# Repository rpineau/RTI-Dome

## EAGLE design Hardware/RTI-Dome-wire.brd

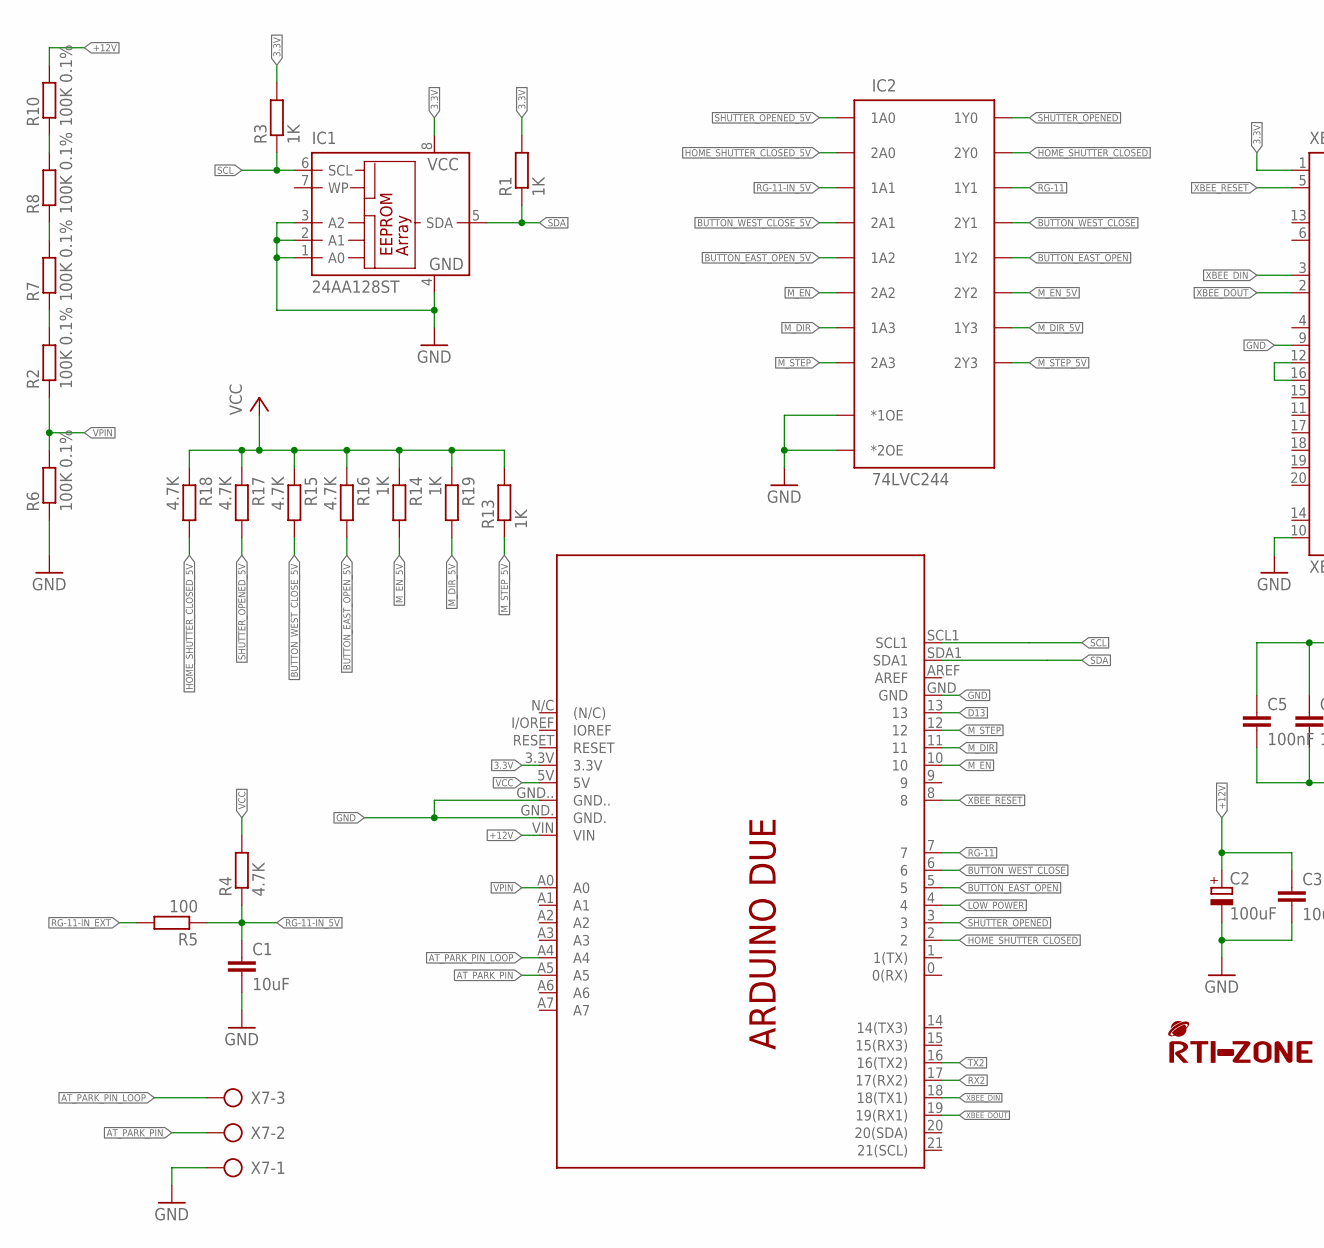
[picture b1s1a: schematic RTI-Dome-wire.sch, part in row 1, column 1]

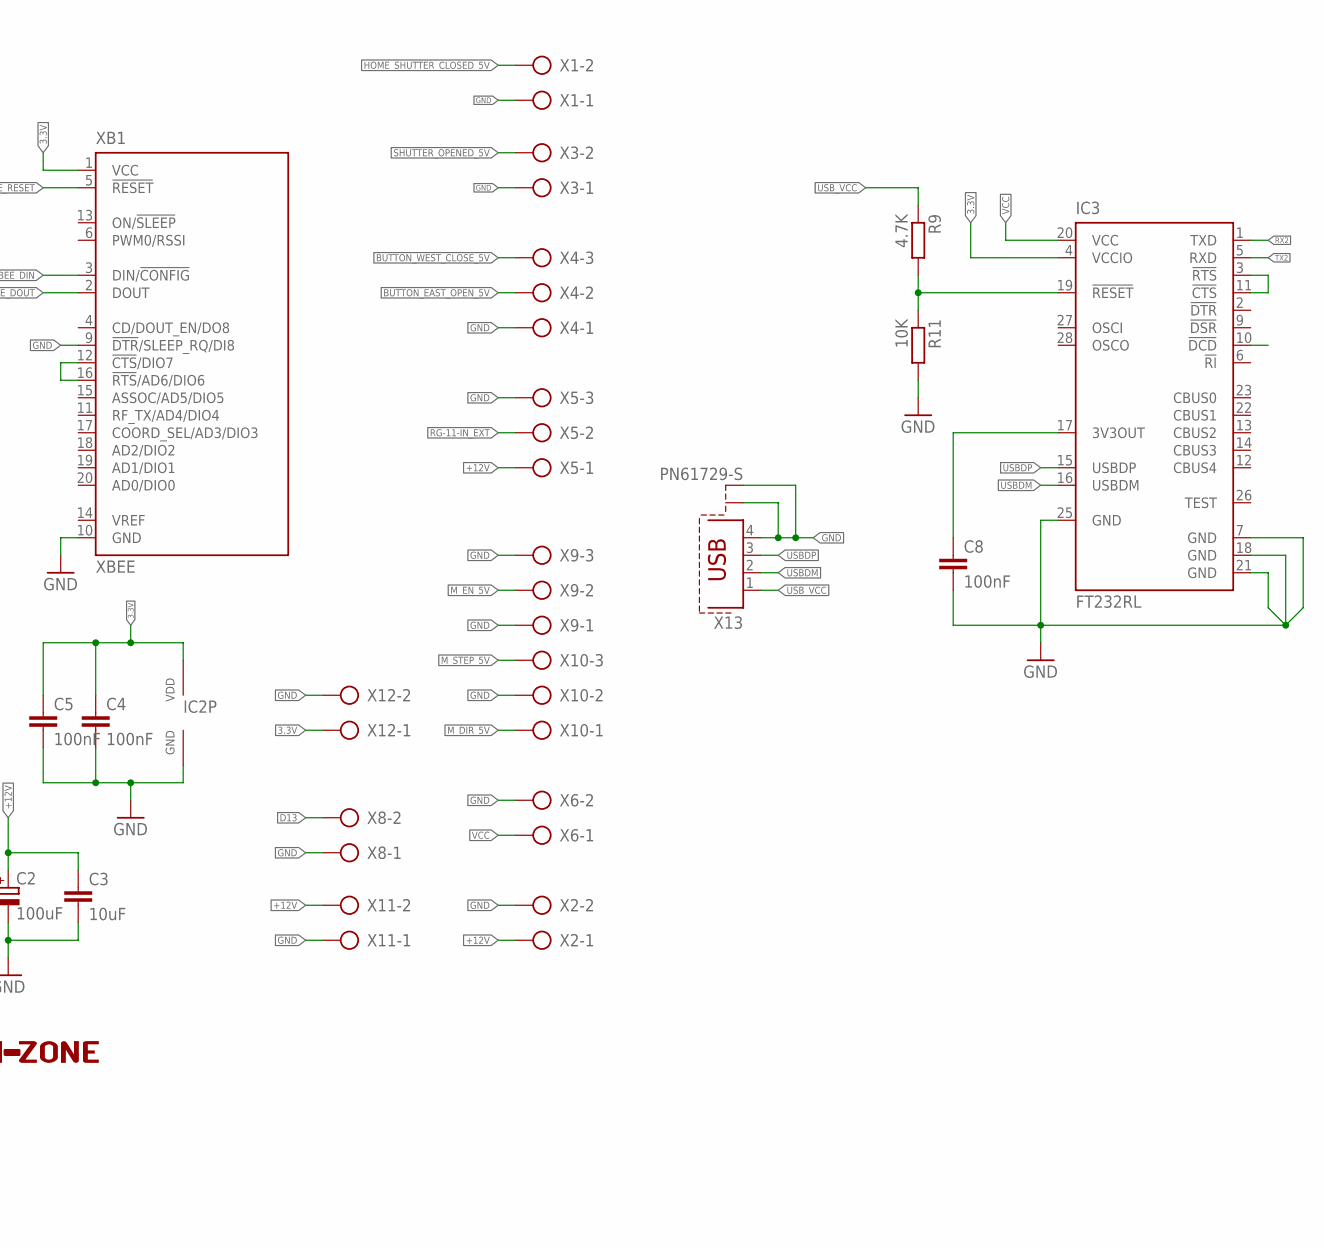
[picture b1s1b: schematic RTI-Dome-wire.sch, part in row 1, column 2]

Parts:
C1, C3: 10uF; C0805
C2: 100uF; UD-10X10_NICHICON
C4, C5, C8: 100nF; C0805
IC1: 24AA128ST; TSSOP8
IC2: 74LVC244; TSSOP20
IC3: FT232RL; SSOP28
PCB1: ARDUINO_DUE_SHIELD_SHORT
R1, R3, R13, R14, R19: 1K; R0805
R2, R6, R7, R8, R10: 100K 0.1%; R0805
R4, R9, R15, R16, R17, R18: 4.7K; R0805
R5: 100; R0805
R11: 10K; R0805
U$4: RTI-LOGO_BIG; LOGO_BIG
X1, X2, X3, X6, X8, X11, X12: AK500/2
X4, X5, X7, X9, X10: AK500/3
X13: PN61729-S
XB1: XBEE

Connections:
3.3V: C4.1, C5.1, IC1.8 (VCC), IC2.P$20 (VDD), IC3.4 (VCCIO), PCB1.3.3V, R1.2, R3.2, X12.1, XB1.1 (VCC)
+12V: C2.+, C3.1, PCB1.VIN, R10.2, X2.1, X5.1, X11.2
AT_PARK_PIN: PCB1.A5, X7.2
AT_PARK_PIN_LOOP: PCB1.A4, X7.3
BUTTON_EAST_OPEN: IC2.P$14 (1Y2), PCB1.5
BUTTON_EAST_OPEN_5V: IC2.P$6 (1A2), R16.2, X4.2
BUTTON_WEST_CLOSE: IC2.P$5 (2Y1), PCB1.6
BUTTON_WEST_CLOSE_5V: IC2.P$15 (2A1), R15.2, X4.3
D13: PCB1.13, X8.2
GND: C1.2, C2.-, C3.2, C4.2, C5.2, C8.2, IC1.1 (A0), IC1.2 (A1), IC1.3 (A2), IC1.4 (GND), IC2.P$1 (*1OE), IC2.P$10 (GND), IC2.P$19 (*2OE), IC3.7 (GND), IC3.18 (GND), IC3.21 (GND), IC3.25 (GND), PCB1.GND, PCB1.GND., PCB1.GND.., R6.1, R11.2, X1.1, X2.2, X3.1, X4.1, X5.3, X6.2, X7.1, X8.1, X9.1, X9.3, X10.2, X11.1, X12.2, X13.4, X13.S1, X13.S2, XB1.9 (!DTR!/SLEEP_RQ/DI8), XB1.10 (GND)
HOME_SHUTTER_CLOSED: IC2.P$3 (2Y0), PCB1.2
HOME_SHUTTER_CLOSED_5V: IC2.P$17 (2A0), R18.2, X1.2
LOW_POWER: PCB1.4
M_DIR: IC2.P$8 (1A3), PCB1.11
M_DIR_5V: IC2.P$12 (1Y3), R19.2, X10.1
M_EN: IC2.P$13 (2A2), PCB1.10
M_EN_5V: IC2.P$7 (2Y2), R14.2, X9.2
M_STEP: IC2.P$11 (2A3), PCB1.12
M_STEP_5V: IC2.P$9 (2Y3), R13.1, X10.3
unnamed: IC3.19 (!RESET), R9.2, R11.1
unnamed: R7.2, R8.1
unnamed: R8.2, R10.1
unnamed: IC3.3 (!RTS), IC3.11 (!CTS)
unnamed: R2.2, R7.1
unnamed: C8.1, IC3.17 (3V3OUT)
unnamed: XB1.12 (!CTS!/DIO7), XB1.16 (!RTS!/AD6/DIO6)
RG-11: IC2.P$16 (1Y1), PCB1.7
RG-11-IN_5V: C1.1, IC2.P$4 (1A1), R4.1, R5.1
RG-11-IN_EXT: R5.2, X5.2
RX2: IC3.1 (TXD), PCB1.17 (17(RX2))
SCL: IC1.6 (SCL), PCB1.SCL1, R3.1
SDA: IC1.5 (SDA), PCB1.SDA1, R1.1
SHUTTER_OPENED: IC2.P$18 (1Y0), PCB1.3
SHUTTER_OPENED_5V: IC2.P$2 (1A0), R17.2, X3.2
TX2: IC3.5 (RXD), PCB1.16 (16(TX2))
USBDM: IC3.16 (USBDM), X13.2
USBDP: IC3.15 (USBDP), X13.3
USB_VCC: R9.1, X13.1
VCC: IC3.20 (VCC), PCB1.5V, R4.2, R13.2, R14.1, R15.1, R16.1, R17.1, R18.1, R19.1, X6.1
VPIN: PCB1.A0, R2.1, R6.2
XBEE_DIN: PCB1.18 (18(TX1)), XB1.3 (DIN/!CONFIG)
XBEE_DOUT: PCB1.19 (19(RX1)), XB1.2 (DOUT)
XBEE_RESET: PCB1.8, XB1.5 (!RESET)

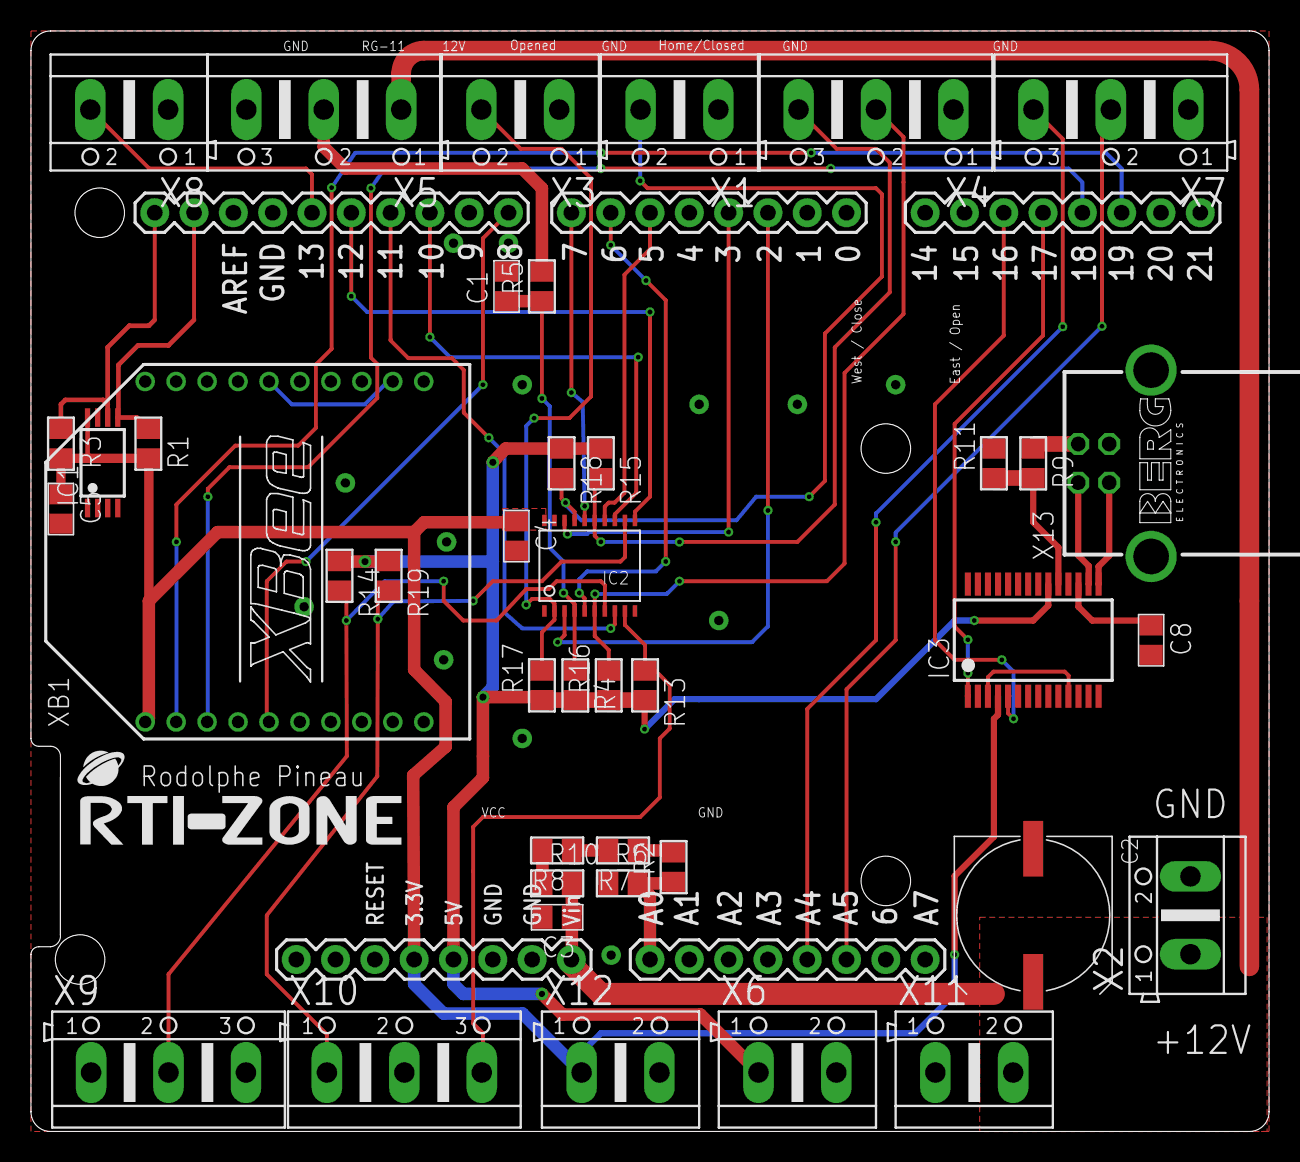
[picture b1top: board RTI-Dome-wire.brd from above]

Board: 2 copper layers, 80.0 x 71.1 mm, 43 parts (0 on the bottom side), 42 nets.

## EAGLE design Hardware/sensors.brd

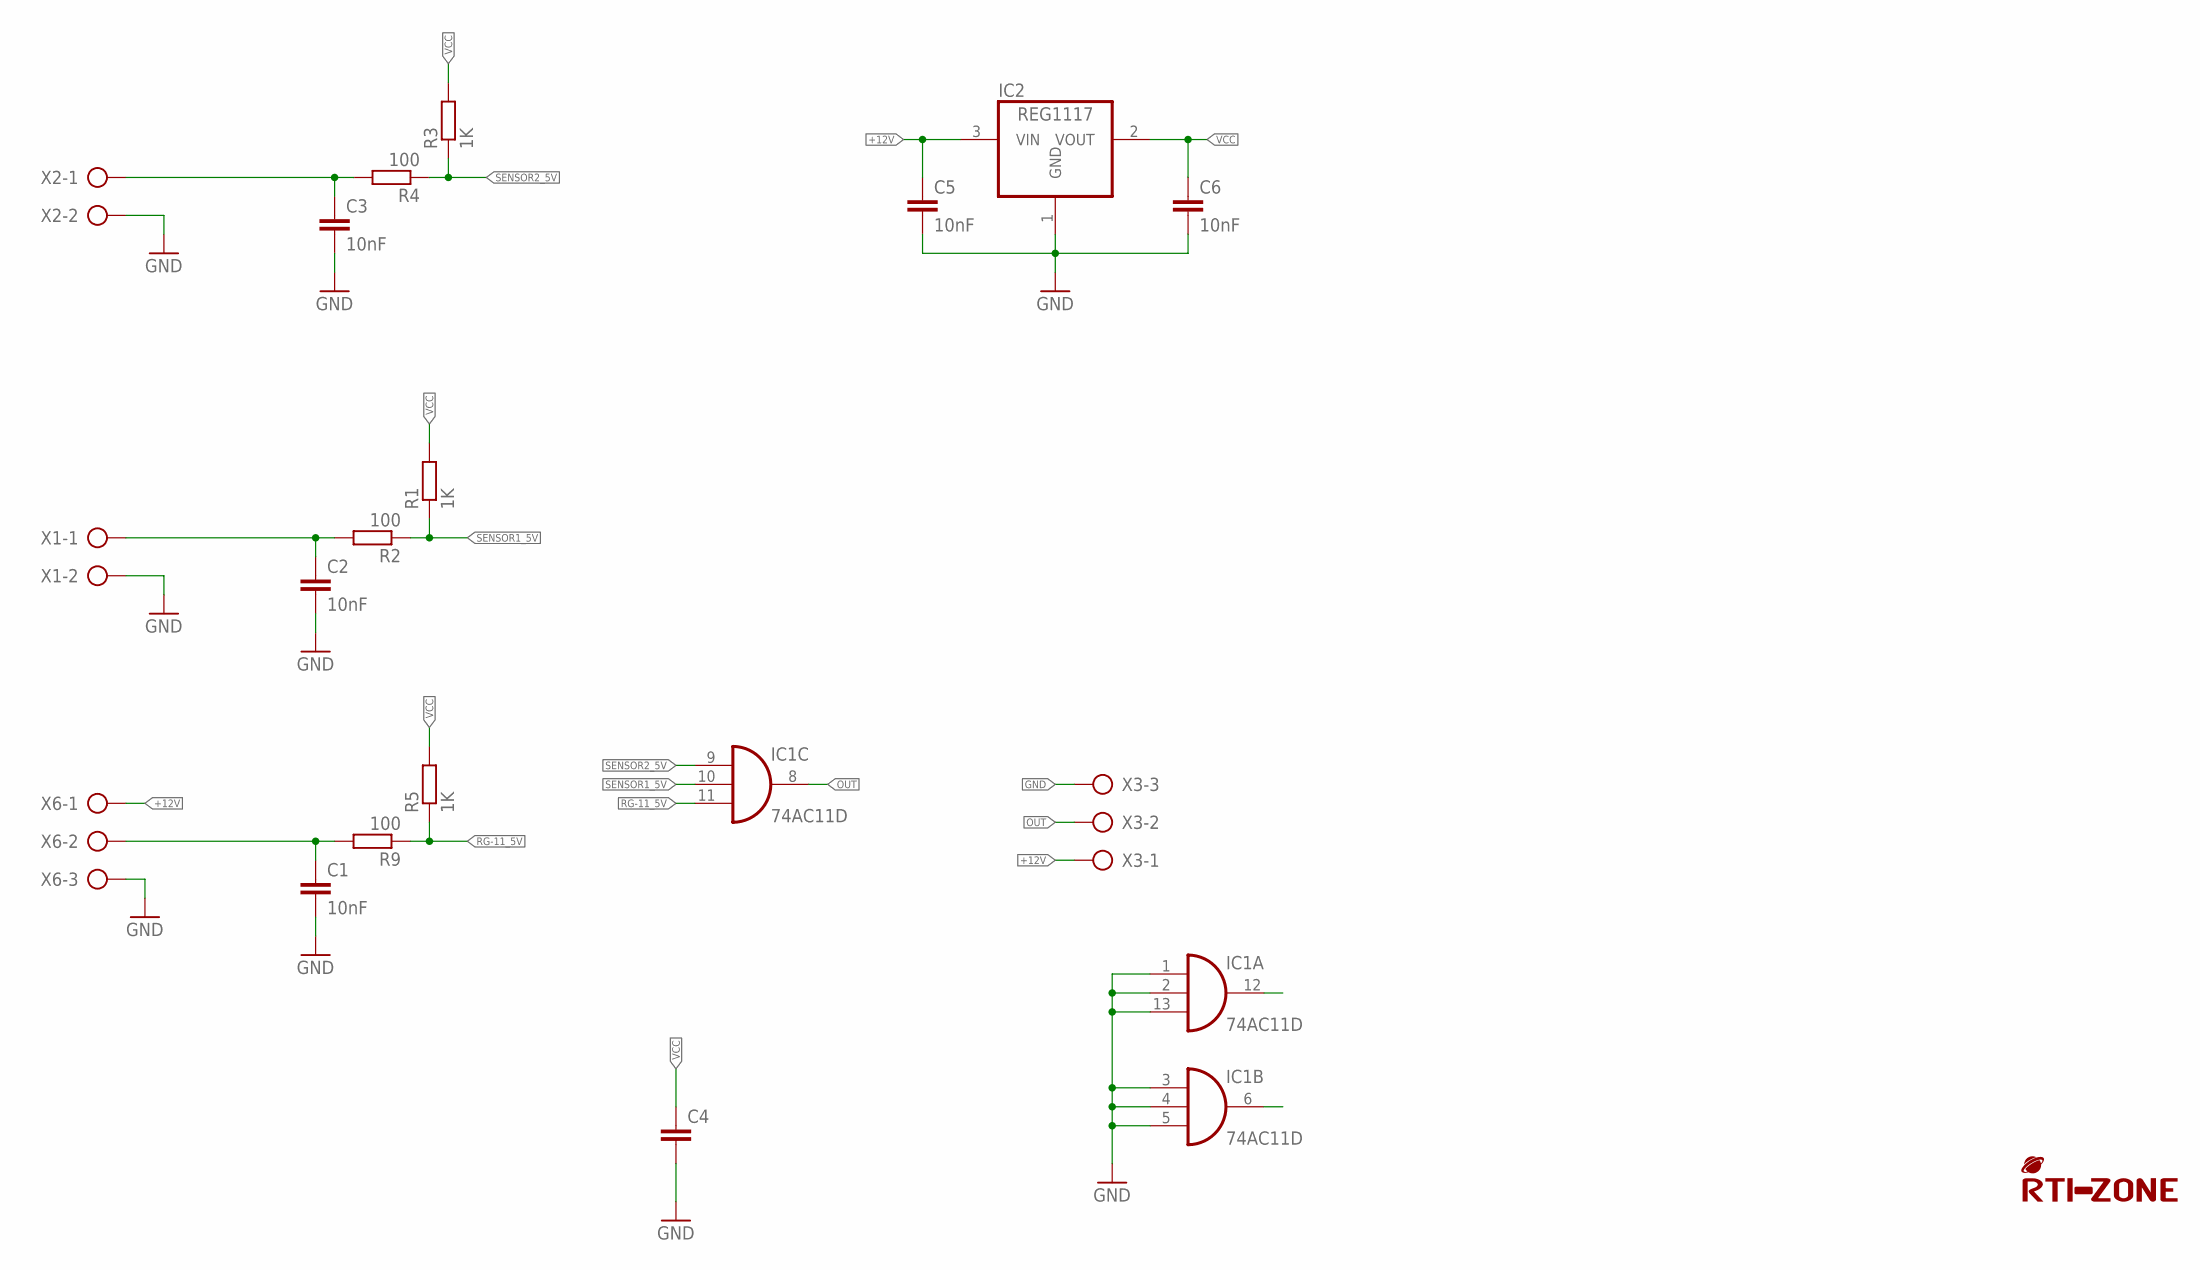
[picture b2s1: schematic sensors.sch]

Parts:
C1, C2, C3, C5, C6: 10nF; C0805
C4: C-EU'1206'; C1206
IC1: 74AC11D; SO14
IC2: REG1117; SOT223
R1, R3, R5: 1K; R0805
R2, R4, R9: 100; R0805
U$1: RTI-LOGO_BIG; LOGO_BIG
X1, X2: AK500/2
X3, X6: AK500/3

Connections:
+12V: C5.1, IC2.3 (VIN), X3.1, X6.1
GND: C1.2, C2.2, C3.2, C4.2, C5.2, C6.2, IC1.1 (I0), IC1.2 (I1), IC1.3 (I0), IC1.4 (I1), IC1.5 (I2), IC1.7 (GND), IC1.13 (I2), IC2.1 (GND), X1.2, X2.2, X3.3, X6.3
OUT: IC1.8 (O), X3.2
RG-11: C1.1, R9.2, X6.2
RG-11_5V: IC1.11 (I2), R5.1, R9.1
SENSOR1: C2.1, R2.2, X1.1
SENSOR1_5V: IC1.10 (I1), R1.1, R2.1
SENSOR2: C3.1, R4.2, X2.1
SENSOR2_5V: IC1.9 (I0), R3.1, R4.1
VCC: C4.1, C6.1, IC1.14 (VCC), IC2.2 (VOUT), R1.2, R3.2, R5.2

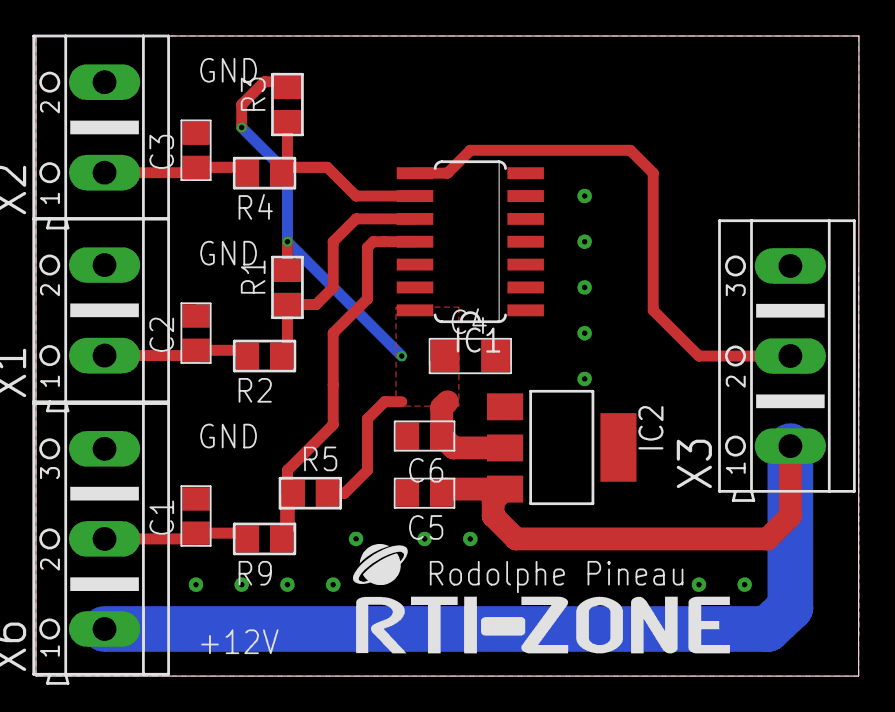
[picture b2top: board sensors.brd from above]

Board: 2 copper layers, 45.7 x 35.6 mm, 19 parts (0 on the bottom side), 10 nets.
